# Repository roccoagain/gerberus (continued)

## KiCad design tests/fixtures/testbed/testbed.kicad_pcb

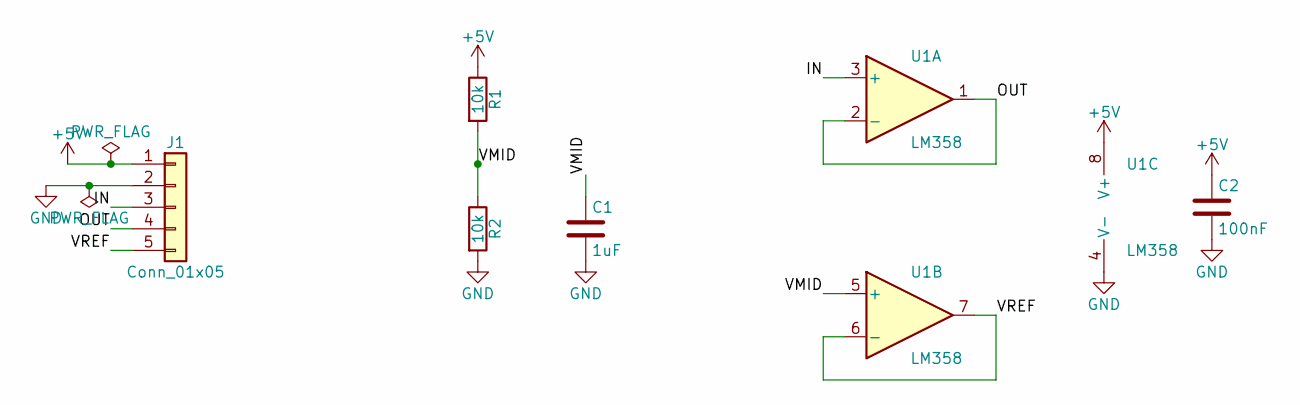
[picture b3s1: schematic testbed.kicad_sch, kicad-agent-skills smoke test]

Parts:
C1: 1uF; C_0603_1608Metric; LCSC C15849
C2: 100nF; C_0603_1608Metric; LCSC C14663
J1: Conn_01x05; PinHeader_1x05_P2.54mm_Vertical; LCSC C2337
R1, R2: 10k; R_0603_1608Metric; LCSC C25804
U1: LM358; SOIC-8_3.9x4.9mm_P1.27mm; MPN LM358DR; LCSC C7950

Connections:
+5V: C2.1, J1.1, R1.1, U1.8 (V+)
/IN: J1.3, U1.3 (+)
/OUT: J1.4, U1.1, U1.2 (-)
/VMID: C1.1, R1.2, R2.1, U1.5 (+)
/VREF: J1.5, U1.6 (-), U1.7
GND: C1.2, C2.2, J1.2, R2.2, U1.4 (V-)

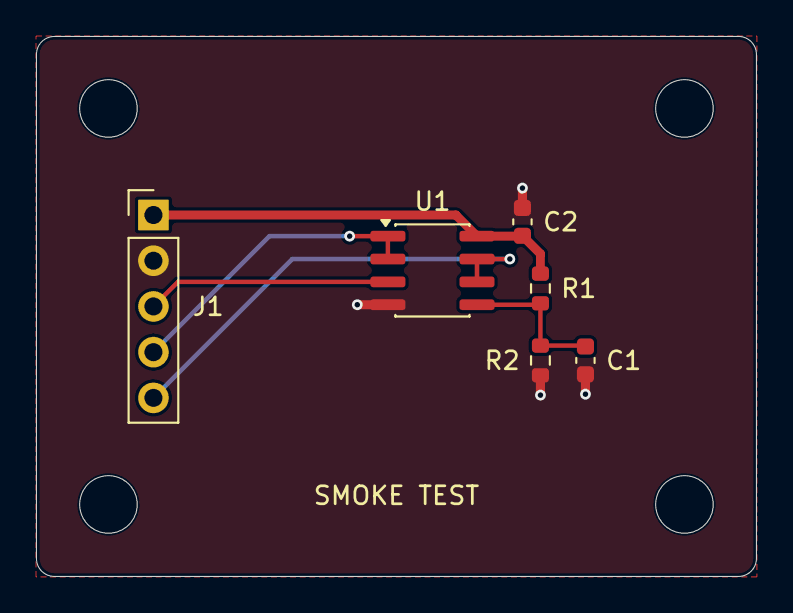
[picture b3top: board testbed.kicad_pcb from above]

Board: 2 copper layers, 40.0 x 30.0 mm, 10 parts (0 on the bottom side), 6 nets.

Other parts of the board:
H1, H2, H3, H4: MountingHole_3.2mm_M3

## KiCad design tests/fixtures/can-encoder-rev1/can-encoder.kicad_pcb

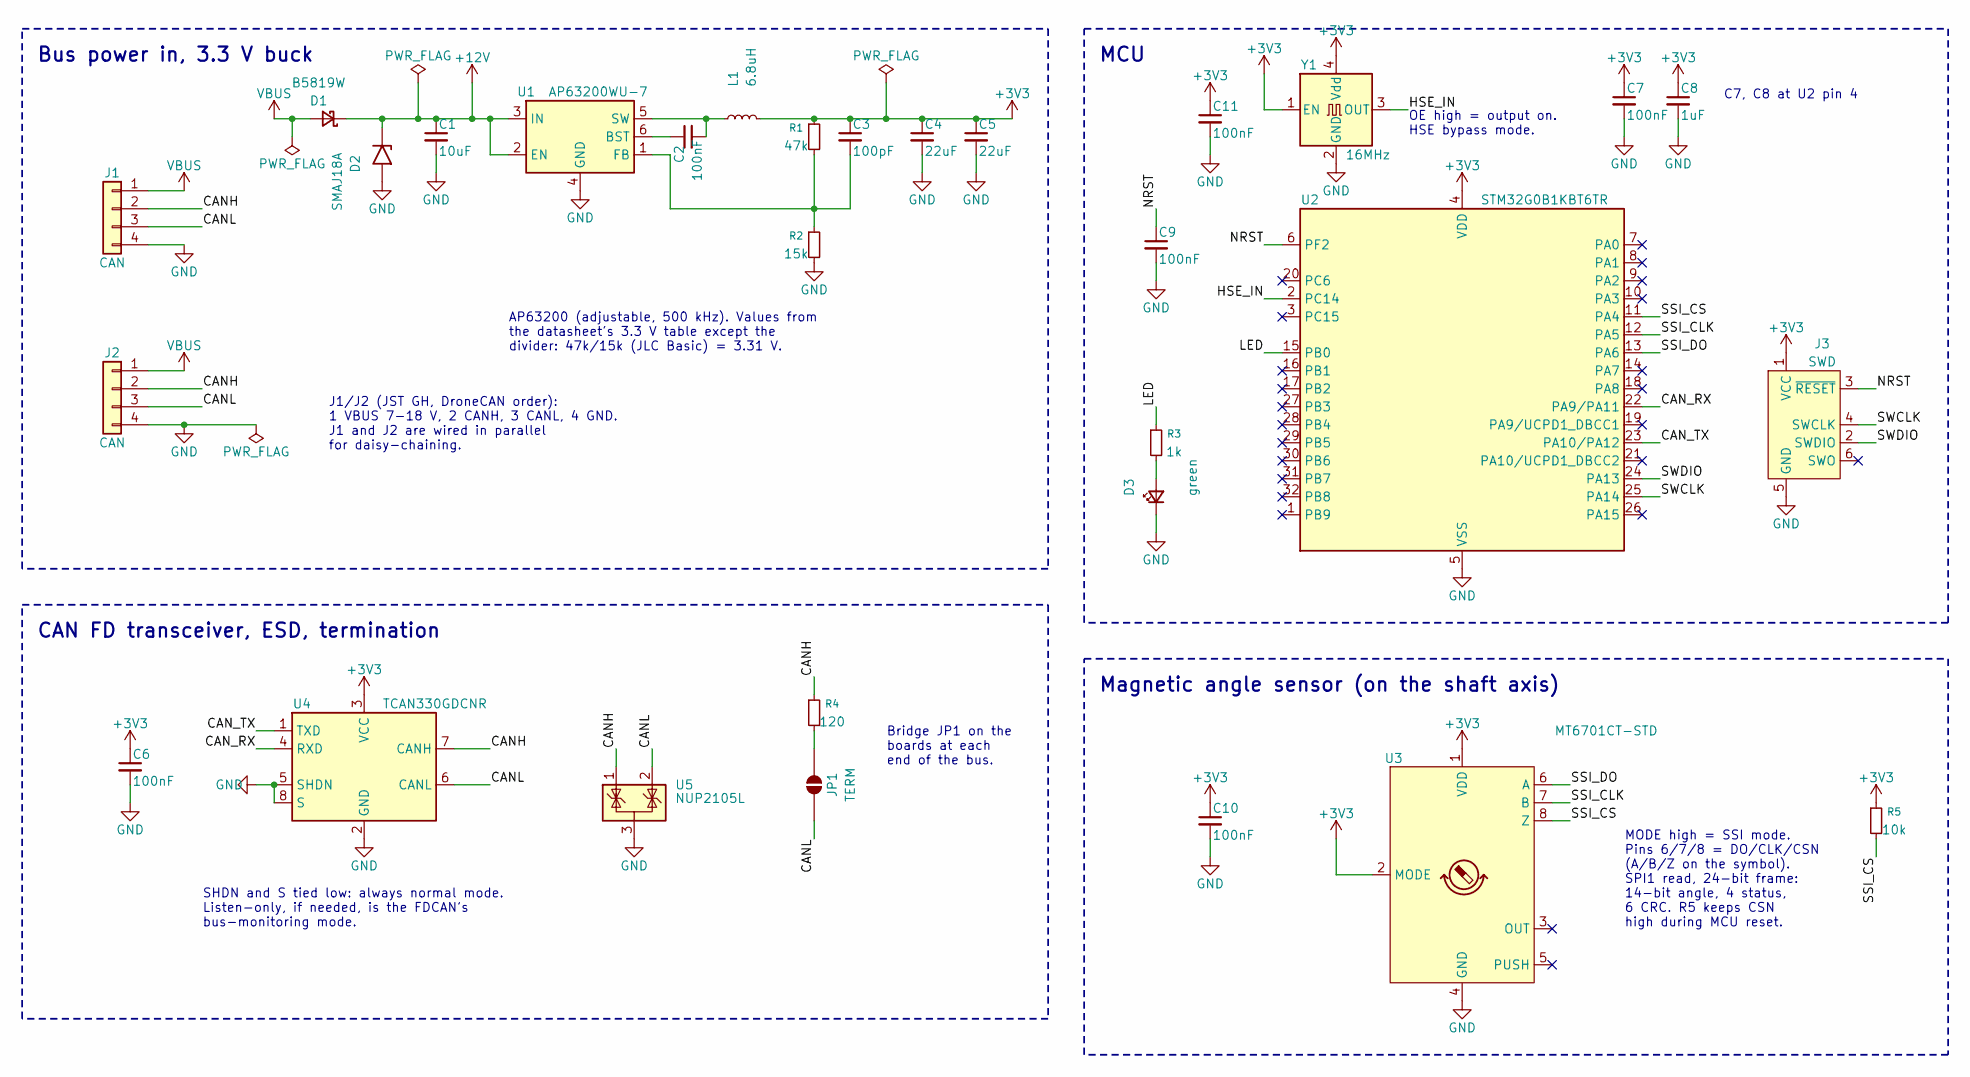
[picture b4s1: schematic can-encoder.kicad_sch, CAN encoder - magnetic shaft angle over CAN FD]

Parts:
C1: 10uF; C_0805_2012Metric; Voltage 50V; MPN GRM21BR61H106KE43L; LCSC C440198
C2, C6, C7, C9, C10, C11: 100nF; C_0402_1005Metric; Voltage 16V; MPN CL05B104KO5NNNC; LCSC C1525
C3: 100pF; C_0402_1005Metric; Voltage 50V; MPN 0402CG101J500NT; LCSC C1546
C4, C5: 22uF; C_0805_2012Metric; Voltage 25V; MPN CL21A226MAQNNNE; LCSC C45783
C8: 1uF; C_0402_1005Metric; Voltage 25V; MPN CL05A105KA5NQNC; LCSC C52923
D1: B5819W; D_SOD-123; MPN B5819W SL; LCSC C8598
D2: SMAJ18A; D_SMA; MPN SMAJ18A; LCSC C173513
D3: green; LED_0805_2012Metric; MPN KT-0805G; LCSC C2297
J1, J2: CAN; JST_GH_SM04B-GHS-TB_1x04-1MP_P1.25mm_Horizontal; MPN SM04B-GHS-TB(LF)(SN); LCSC C189895
J3: SWD; Tag-Connect_TC2030-IDC-NL_2x03_P1.27mm_Vertical
JP1: TERM; SolderJumper-2_P1.3mm_Open_RoundedPad1.0x1.5mm
L1: 6.8uH; L_Changjiang_FNR4030S; MPN FNR4030S6R8MT; LCSC C167876
R1: 47k; R_0402_1005Metric; MPN 0402WGF4702TCE; LCSC C25792
R2: 15k; R_0402_1005Metric; MPN 0402WGF1502TCE; LCSC C25756
R3: 1k; R_0402_1005Metric; MPN 0402WGF1001TCE; LCSC C11702
R4: 120; R_0402_1005Metric; MPN 0402WGF1200TCE; LCSC C25079
R5: 10k; R_0402_1005Metric; MPN 0402WGF1002TCE; LCSC C25744
U1: AP63200WU-7; TSOT-23-6; MPN AP63200WU-7; LCSC C2071868
U2: STM32G0B1KBT6TR; LQFP-32_7x7mm_P0.8mm; MPN STM32G0B1KBT6TR; LCSC C7021416
U3: MT6701CT-STD; SOIC-8_3.9x4.9mm_P1.27mm; MPN MT6701CT-STD-R; LCSC C3003196
U4: TCAN330GDCNR; SOT-23-8; MPN TCAN330GDCNR; LCSC C191006
U5: NUP2105L; SOT-23; MPN NUP2105LT1G; LCSC C14486
Y1: 16MHz; Oscillator_SMD_SiT_PQFN-4Pin_2.0x1.6mm; MPN OT201616MJBA4SL; LCSC C669078

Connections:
+3V3: C3.1, C4.1, C5.1, C6.1, C7.1, C8.1, C10.1, C11.1, J3.1 (VCC), L1.2, R1.1, R5.1, U2.4 (VDD), U3.1 (VDD), U3.2 (MODE), U4.3 (VCC), Y1.1 (EN), Y1.4 (Vdd)
+12V: C1.1, D1.1 (K), D2.1 (A1), U1.2 (EN), U1.3 (IN)
/CANH: J1.2, J2.2, R4.1, U4.7 (CANH), U5.1 (K)
/CANL: J1.3, J2.3, JP1.1 (A), U4.6 (CANL), U5.2 (K)
/CAN_RX: U2.22 (PA9/PA11), U4.4 (RXD)
/CAN_TX: U2.23 (PA10/PA12), U4.1 (TXD)
/HSE_IN: U2.2 (PC14), Y1.3 (OUT)
/LED: R3.1, U2.15 (PB0)
/NRST: C9.1, J3.3 (~RESET), U2.6 (PF2)
/SSI_CLK: U2.12 (PA5), U3.7 (B)
/SSI_CS: R5.2, U2.11 (PA4), U3.8 (Z)
/SSI_DO: U2.13 (PA6), U3.6 (A)
/SWCLK: J3.4 (SWCLK), U2.25 (PA14)
/SWDIO: J3.2 (SWDIO), U2.24 (PA13)
GND: C1.2, C4.2, C5.2, C6.2, C7.2, C8.2, C9.2, C10.2, C11.2, D2.2 (A2), D3.1 (K), J1.4, J2.4, J3.5 (GND), R2.2, U1.4 (GND), U2.5 (VSS), U3.4 (GND), U4.2 (GND), U4.5 (SHDN), U4.8 (S), U5.3 (A), Y1.2 (GND)
unnamed: D3.2 (A), R3.2
unnamed: JP1.2 (B), R4.2
unnamed: C2.1, U1.6 (BST)
unnamed: C3.2, R1.2, R2.1, U1.1 (FB)
unnamed: C2.2, L1.1, U1.5 (SW)
VBUS: D1.2 (A), J1.1, J2.1

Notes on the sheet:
Bus power in, 3.3 V buck
J1/J2 (JST GH, DroneCAN order): 1 VBUS 7-18 V, 2 CANH, 3 CANL, 4 GND. J1 and J2 are wired in parallel for daisy-chaining.
AP63200 (adjustable, 500 kHz). Values from the datasheet's 3.3 V table except the divider: 47k/15k (JLC Basic) = 3.31 V.
CAN FD transceiver, ESD, termination
Bridge JP1 on the boards at each end of the bus.
SHDN and S tied low: always normal mode. Listen-only, if needed, is the FDCAN's bus-monitoring mode.
MCU
C7, C8 at U2 pin 4
OE high = output on. HSE bypass mode.
Magnetic angle sensor (on the shaft axis)
MODE high = SSI mode. Pins 6/7/8 = DO/CLK/CSN (A/B/Z on the symbol). SPI1 read, 24-bit frame: 14-bit angle, 4 status, 6 CRC. R5 keeps CSN high during MCU reset.

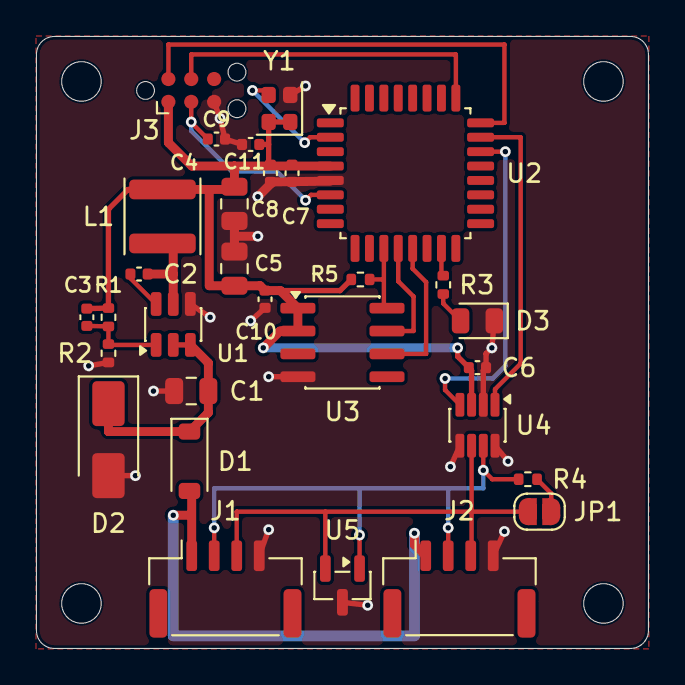
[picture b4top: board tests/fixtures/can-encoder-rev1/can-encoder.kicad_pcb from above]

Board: 2 copper layers, 34.0 x 34.0 mm, 34 parts (0 on the bottom side), 21 nets.

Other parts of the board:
H1, H2, H3, H4: MountingHole_2.2mm_M2

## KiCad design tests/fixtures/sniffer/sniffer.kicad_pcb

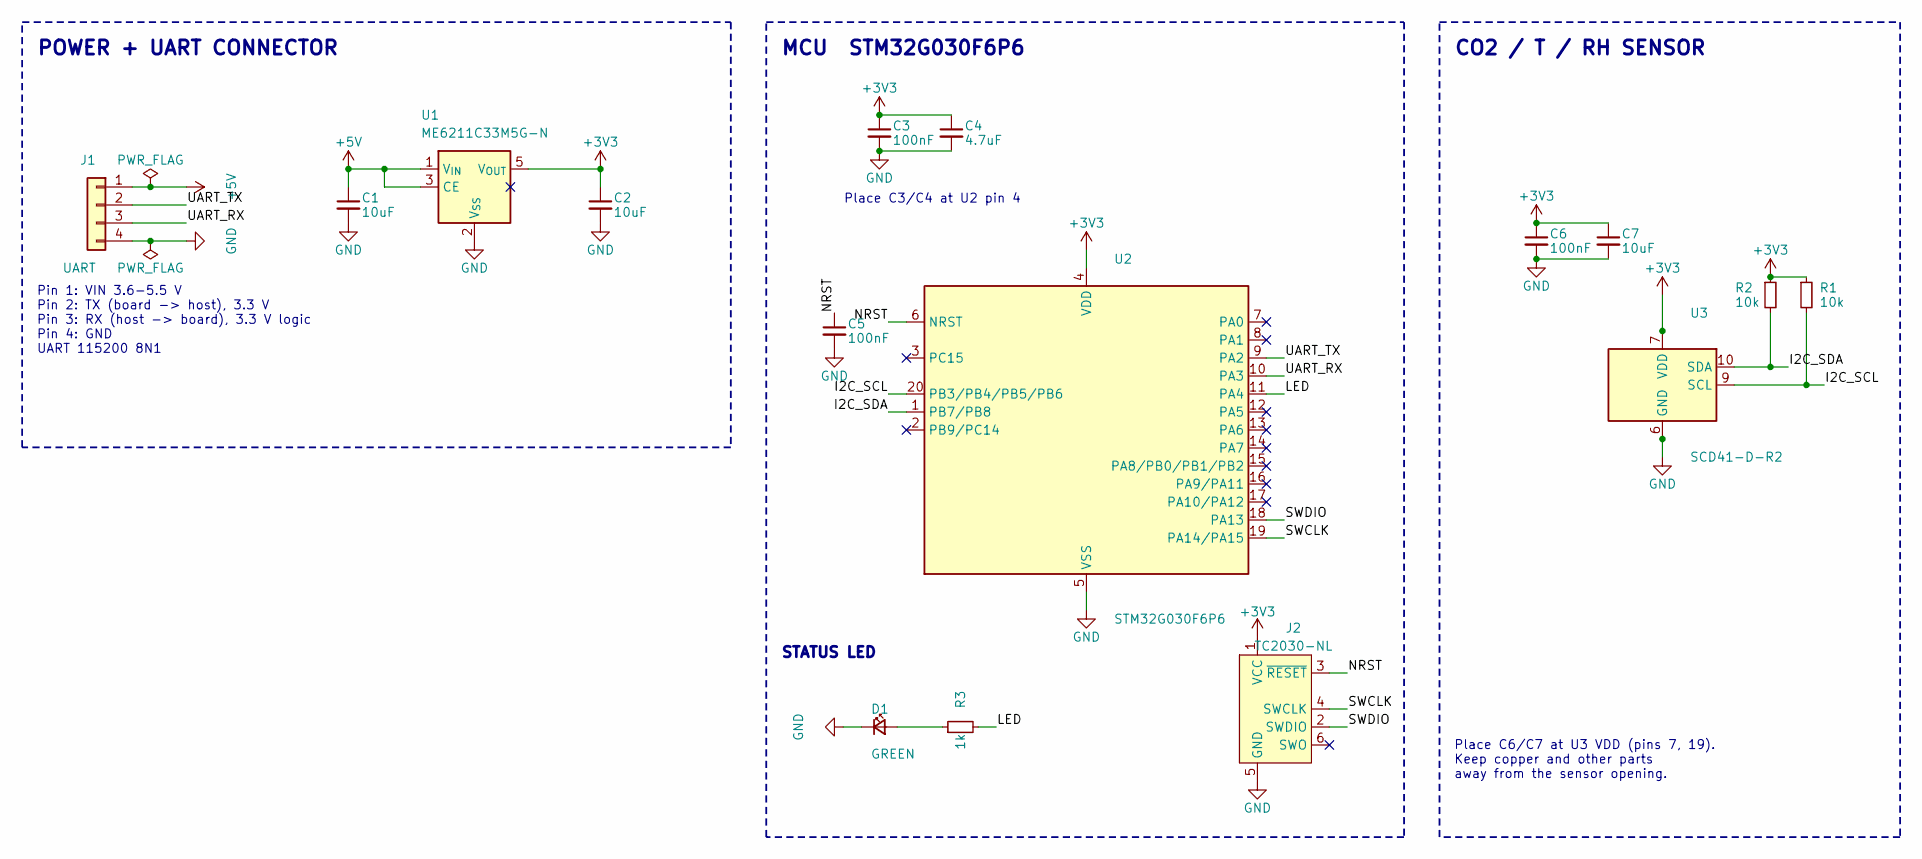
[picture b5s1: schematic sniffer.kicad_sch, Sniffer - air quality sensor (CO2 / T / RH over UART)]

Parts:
C1, C2, C7: 10uF; C_0805_2012Metric; Voltage 25V; MPN CL21A106KAYNNNE; LCSC C15850
C3, C5, C6: 100nF; C_0603_1608Metric; Voltage 50V; MPN CC0603KRX7R9BB104; LCSC C14663
C4: 4.7uF; C_0603_1608Metric; Voltage 16V; MPN CL10A475KO8NNNC; LCSC C19666
D1: GREEN; LED_0805_2012Metric; MPN KT-0805G; LCSC C2297
J1: UART; JST_SH_SM04B-SRSS-TB_1x04-1MP_P1.00mm_Horizontal; MPN SM04B-SRSS-TB(LF)(SN); LCSC C160404
J2: TC2030-NL; Tag-Connect_TC2030-IDC-NL_2x03_P1.27mm_Vertical
R1, R2: 10k; R_0603_1608Metric; MPN 0603WAF1002T5E; LCSC C25804
R3: 1k; R_0603_1608Metric; MPN 0603WAF1001T5E; LCSC C21190
U1: ME6211C33M5G-N; SOT-23-5; MPN ME6211C33M5G-N; LCSC C82942
U2: STM32G030F6P6; TSSOP-20_4.4x6.5mm_P0.65mm; MPN STM32G030F6P6TR; LCSC C529330
U3: SCD41-D-R2; Sensirion_SCD4x-1EP_10.1x10.1mm_P1.25mm_EP4.8x4.8mm; MPN SCD41-D-R2; LCSC C3659294

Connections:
+3V3: C2.1, C3.1, C4.1, C6.1, C7.1, J2.1 (VCC), R1.1, R2.1, U1.5 (V_{OUT}), U2.4 (VDD), U3.7 (VDD), U3.19 (VDD)
+5V: C1.1, J1.1, U1.1 (V_{IN}), U1.3 (CE)
/I2C_SCL: R1.2, U2.20 (PB3/PB4/PB5/PB6), U3.9 (SCL)
/I2C_SDA: R2.2, U2.1 (PB7/PB8), U3.10 (SDA)
/LED: R3.2, U2.11 (PA4)
/NRST: C5.1, J2.3 (~RESET), U2.6 (NRST)
/SWCLK: J2.4 (SWCLK), U2.19 (PA14/PA15)
/SWDIO: J2.2 (SWDIO), U2.18 (PA13)
/UART_RX: J1.3, U2.10 (PA3)
/UART_TX: J1.2, U2.9 (PA2)
GND: C1.2, C2.2, C3.2, C4.2, C5.2, C6.2, C7.2, D1.1 (K), J1.4, J2.5 (GND), U1.2 (V_{SS}), U2.5 (VSS), U3.6 (GND), U3.20 (GND), U3.21 (GND)
unnamed: D1.2 (A), R3.1

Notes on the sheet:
POWER + UART CONNECTOR
Pin 1: VIN 3.6-5.5 V Pin 2: TX (board -> host), 3.3 V Pin 3: RX (host -> board), 3.3 V logic Pin 4: GND UART 115200 8N1
MCU STM32G030F6P6
Place C3/C4 at U2 pin 4
STATUS LED
CO2 / T / RH SENSOR
Place C6/C7 at U3 VDD (pins 7, 19). Keep copper and other parts away from the sensor opening.

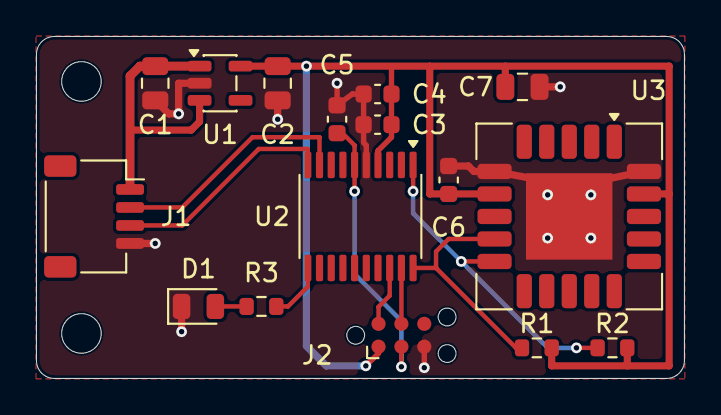
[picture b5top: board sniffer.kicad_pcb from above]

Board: 2 copper layers, 36.0 x 19.0 mm, 18 parts (0 on the bottom side), 12 nets.

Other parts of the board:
H1, H2: MountingHole_2.2mm_M2

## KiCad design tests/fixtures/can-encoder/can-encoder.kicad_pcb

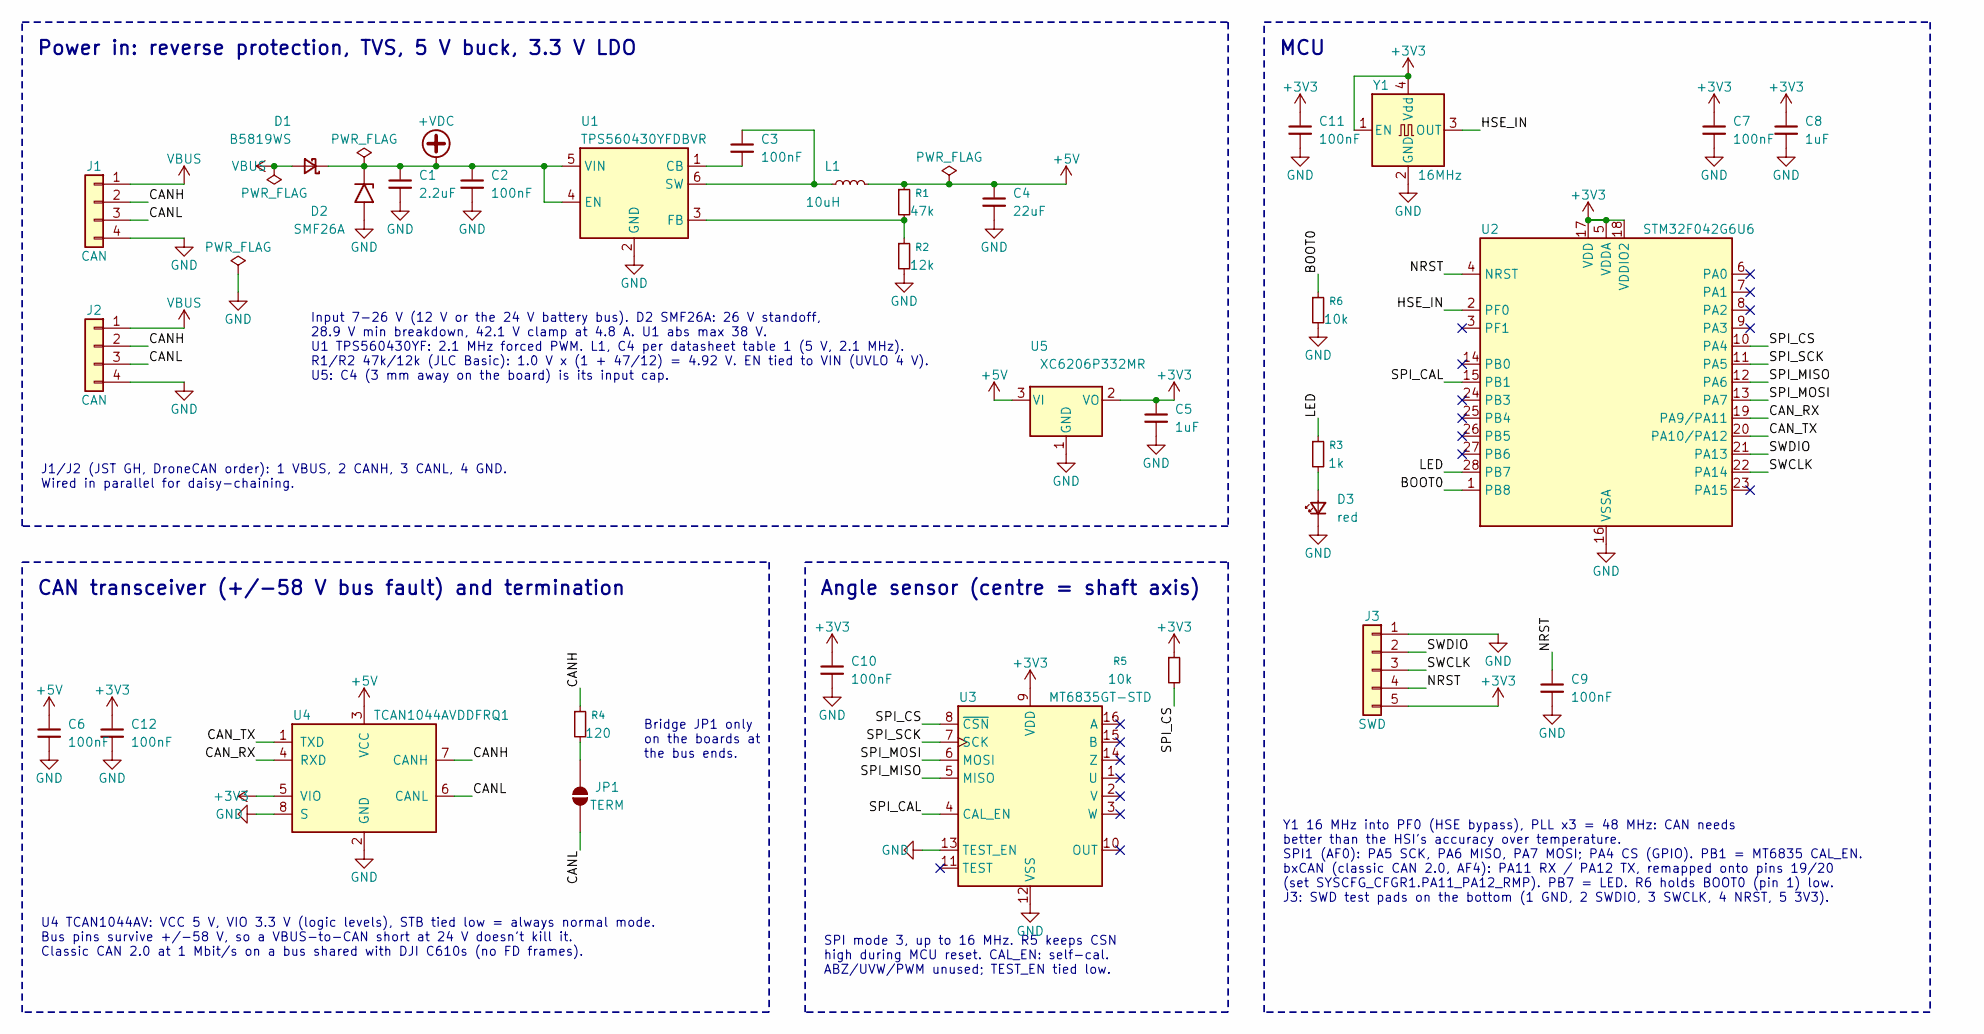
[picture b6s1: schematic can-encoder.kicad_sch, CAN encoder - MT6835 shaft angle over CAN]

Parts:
C1: 2.2uF; C_0805_2012Metric; Voltage 50V; MPN CC0805KKX7R9BB225; LCSC C125847
C2: 100nF; C_0402_1005Metric; Voltage 50V; MPN CL05B104KB54PNC; LCSC C307331
C3, C6, C7, C9, C10, C11, C12: 100nF; C_0402_1005Metric; Voltage 16V; MPN CL05B104KO5NNNC; LCSC C1525
C4: 22uF; C_0805_2012Metric; Voltage 25V; MPN CL21A226MAQNNNE; LCSC C45783
C5, C8: 1uF; C_0402_1005Metric; Voltage 25V; MPN CL05A105KA5NQNC; LCSC C52923
D1: B5819WS; D_SOD-323; MPN B5819WS; LCSC C22624
D2: SMF26A; D_SOD-123F; MPN SMF26A; LCSC C123789
D3: red; LED_0603_1608Metric; MPN KT-0603R; LCSC C2286
J1, J2: CAN; JST_GH_SM04B-GHS-TB_1x04-1MP_P1.25mm_Horizontal; MPN SM04B-GHS-TB(LF)(SN); LCSC C189895
J3: SWD; SWD_Pads_1x05_P1.27mm
JP1: TERM; SolderJumper-2_P1.3mm_Open_RoundedPad1.0x1.5mm
L1: 10uH; L_Sunlord_SWPA252012S; MPN SWPA252012S100MT; LCSC C37428
R1: 47k; R_0402_1005Metric; MPN 0402WGF4702TCE; LCSC C25792
R2: 12k; R_0402_1005Metric; MPN 0402WGF1202TCE; LCSC C25752
R3: 1k; R_0402_1005Metric; MPN 0402WGF1001TCE; LCSC C11702
R4: 120; R_0402_1005Metric; MPN 0402WGF1200TCE; LCSC C25079
R5, R6: 10k; R_0402_1005Metric; MPN 0402WGF1002TCE; LCSC C25744
U1: TPS560430YFDBVR; SOT-23-6; MPN TPS560430YFDBVR; LCSC C962155
U2: STM32F042G6U6; QFN-28_4x4mm_P0.5mm; MPN STM32F042G6U6TR; LCSC C2971720
U3: MT6835GT-STD; TSSOP-16_4.4x5mm_P0.65mm; MPN MT6835GT-STD-R; LCSC C2932578
U4: TCAN1044AVDDFRQ1; SOT-23-8; MPN TCAN1044AVDDFRQ1; LCSC C3236207
U5: XC6206P332MR; SOT-23-3; MPN XC6206P332MR-G; LCSC C5446
Y1: 16MHz; Oscillator_SMD_SiT_PQFN-4Pin_2.0x1.6mm; MPN OT201616MJBA4SL; LCSC C669078

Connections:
+3V3: C5.1, C7.1, C8.1, C10.1, C11.1, C12.1, J3.5, R5.1, U2.5 (VDDA), U2.17 (VDD), U2.18 (VDDIO2), U3.9 (VDD), U4.5 (VIO), U5.2 (VO), Y1.1 (EN), Y1.4 (Vdd)
+5V: C4.1, C6.1, L1.2, R1.1, U4.3 (VCC), U5.3 (VI)
+VDC: C1.1, C2.1, D1.1 (K), D2.1 (A1), U1.4 (EN), U1.5 (VIN)
/BOOT0: R6.1, U2.1 (PB8)
/CANH: J1.2, J2.2, R4.1, U4.7 (CANH)
/CANL: J1.3, J2.3, JP1.1 (A), U4.6 (CANL)
/CAN_RX: U2.19 (PA9/PA11), U4.4 (RXD)
/CAN_TX: U2.20 (PA10/PA12), U4.1 (TXD)
/HSE_IN: U2.2 (PF0), Y1.3 (OUT)
/LED: R3.1, U2.28 (PB7)
/NRST: C9.1, J3.4, U2.4 (NRST)
/SPI_CAL: U2.15 (PB1), U3.4 (CAL_EN)
/SPI_CS: R5.2, U2.10 (PA4), U3.8 (~CSN)
/SPI_MISO: U2.12 (PA6), U3.5 (MISO)
/SPI_MOSI: U2.13 (PA7), U3.6 (MOSI)
/SPI_SCK: U2.11 (PA5), U3.7 (SCK)
/SWCLK: J3.3, U2.22 (PA14)
/SWDIO: J3.2, U2.21 (PA13)
GND: C1.2, C2.2, C4.2, C5.2, C6.2, C7.2, C8.2, C9.2, C10.2, C11.2, C12.2, D2.2 (A2), D3.1 (K), J1.4, J2.4, J3.1, R2.2, R6.2, U1.2 (GND), U2.16 (VSSA), U3.12 (VSS), U3.13 (TEST_EN), U4.2 (GND), U4.8 (S), U5.1 (GND), Y1.2 (GND)
unnamed: D3.2 (A), R3.2
unnamed: JP1.2 (B), R4.2
unnamed: C3.2, U1.1 (CB)
unnamed: R1.2, R2.1, U1.3 (FB)
unnamed: C3.1, L1.1, U1.6 (SW)
VBUS: D1.2 (A), J1.1, J2.1

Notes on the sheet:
Power in: reverse protection, TVS, 5 V buck, 3.3 V LDO
Input 7-26 V (12 V or the 24 V battery bus). D2 SMF26A: 26 V standoff, 28.9 V min breakdown, 42.1 V clamp at 4.8 A. U1 abs max 38 V. U1 TPS560430YF: 2.1 MHz forced PWM. L1, C4 per datasheet table 1 (5 V, 2.1 MHz). R1/R2 47k/12k (JLC Basic): 1.0 V x (1 + 47/12) = 4.92 V. EN tied to VIN (UVLO 4 V). U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
J1/J2 (JST GH, DroneCAN order): 1 VBUS, 2 CANH, 3 CANL, 4 GND. Wired in parallel for daisy-chaining.
CAN transceiver (+/-58 V bus fault) and termination
U4 TCAN1044AV: VCC 5 V, VIO 3.3 V (logic levels), STB tied low = always normal mode. Bus pins survive +/-58 V, so a VBUS-to-CAN short at 24 V doesn't kill it. Classic CAN 2.0 at 1 Mbit/s on a bus shared with DJI C610s (no FD frames).
Bridge JP1 only on the boards at the bus ends.
MCU
Y1 16 MHz into PF0 (HSE bypass), PLL x3 = 48 MHz: CAN needs better than the HSI's accuracy over temperature. SPI1 (AF0): PA5 SCK, PA6 MISO, PA7 MOSI; PA4 CS (GPIO). PB1 = MT6835 CAL_EN. bxCAN (classic CAN 2.0, AF4): PA11 RX / PA12 TX, remapped onto pins 19/20 (set SYSCFG_CFGR1.PA11_PA12_RMP). PB7 =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
Angle sensor (centre = shaft axis)
SPI mode 3, up to 16 MHz. R5 keeps CSN high during MCU reset. CAL_EN: self-cal. ABZ/UVW/PWM unused; TEST_EN tied low.

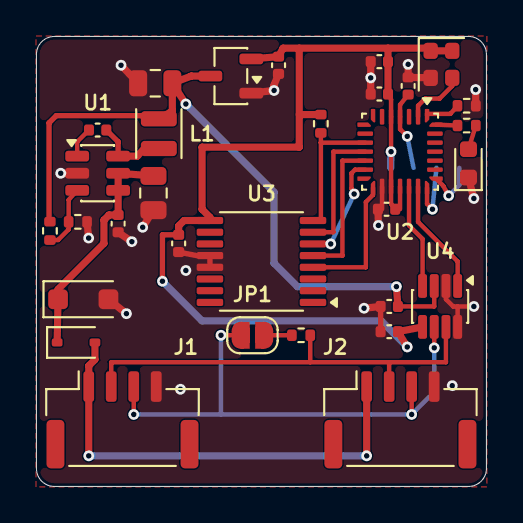
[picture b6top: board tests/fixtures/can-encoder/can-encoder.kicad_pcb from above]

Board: 2 copper layers, 25.0 x 25.0 mm, 32 parts (1 on the bottom side), 25 nets.

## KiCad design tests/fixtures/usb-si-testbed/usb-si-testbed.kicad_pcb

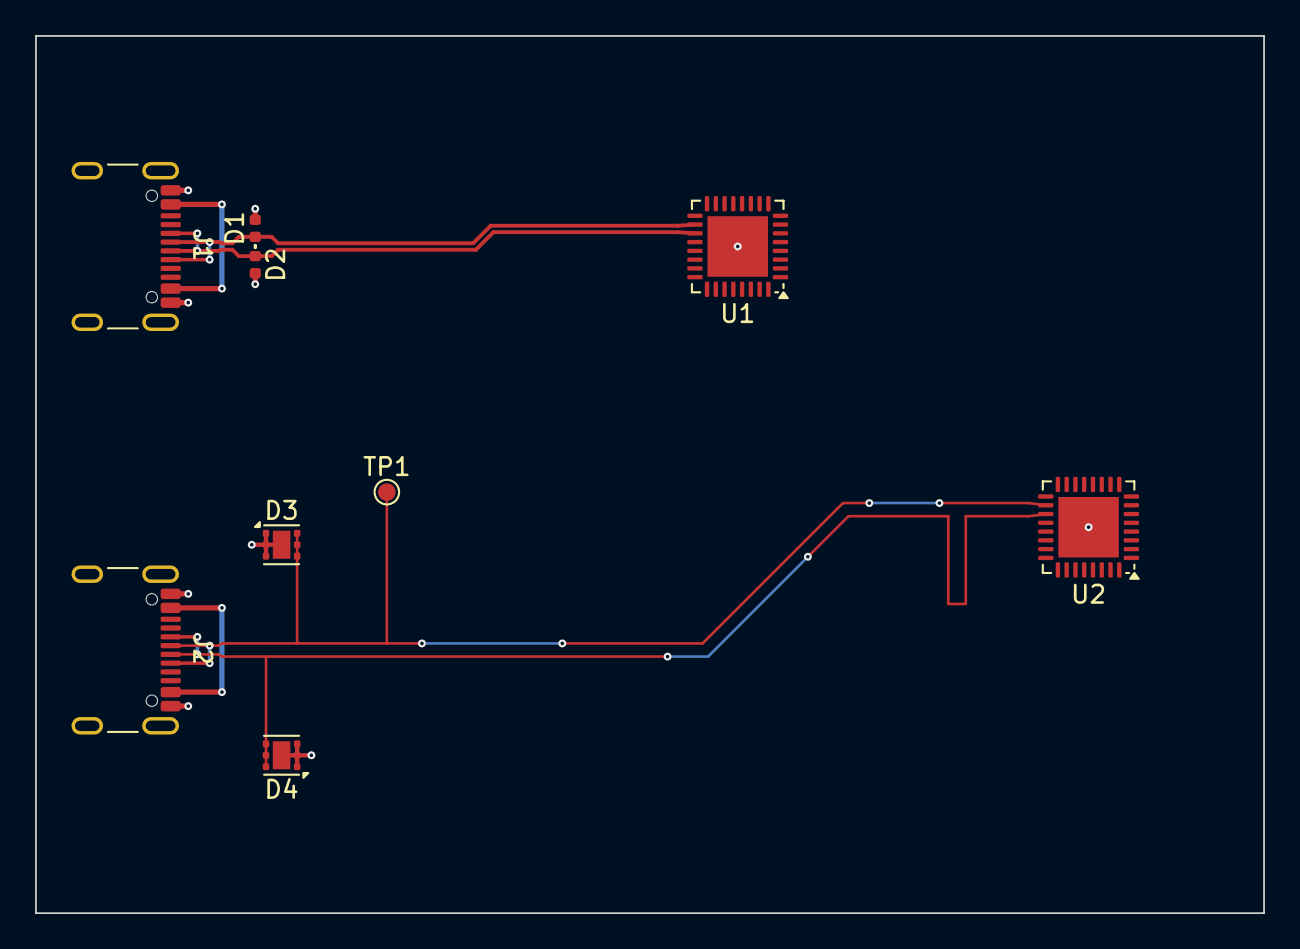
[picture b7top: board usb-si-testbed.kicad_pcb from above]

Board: 4 copper layers, 70.0 x 50.0 mm, 9 parts (0 on the bottom side), 7 nets.

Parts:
D1, D2: TPD1E05U06DPYR; D_0402_1005Metric
D3, D4: TVS0500DRVR; WSON-6-1EP_2x2mm_P0.65mm_EP1x1.6mm
J1, J2: USB4105-GF-A; USB_C_Receptacle_GCT_USB4105-xx-A_16P_TopMnt_Horizontal
TP1: TP; TestPoint_Pad_D1.0mm
U1, U2: TUSB1210BRHBR; Texas_RHB0032E_VQFN-32-1EP_5x5mm_P0.5mm_EP3.45x3.45mm

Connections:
GND: D1.2, D2.2, D3.1, D3.2, D3.3, D3.7, D4.1, D4.2, D4.3, D4.7, J1.A1, J1.A12, J1.B1, J1.B12, J1.S1, J2.A1, J2.A12, J2.B1, J2.B12, J2.S1, U1.33, U2.33
USB1_D+: D1.1, J1.A6, J1.B6, U1.18
USB1_D-: D2.1, J1.A7, J1.B7, U1.19
USB2_D+: D3.4, D3.5, D3.6, J2.A6, J2.B6, TP1.1, U2.18
USB2_D-: D4.4, D4.5, D4.6, J2.A7, J2.B7, U2.19
VBUS1: J1.A4, J1.A9, J1.B4, J1.B9
VBUS2: J2.A4, J2.A9, J2.B4, J2.B9

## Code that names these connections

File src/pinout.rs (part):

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//!
//! Numbers must line up: a symbol pin with no pad never reaches copper, and a datasheet pin with no symbol pin
//! is left floating on the board. Names are compared loosely (case, KiCad markup, alternate functions written
//! as `PA9/PA11`, and a few common synonyms such as `GND`/`VSS`), because symbols rarely copy the datasheet
//! letter for letter. A name that matches a *different* datasheet pin is reported as a swap, which is an
//! error. Any other name difference is a warning for a person to look at, never a pass or a fail by guesswork.
use std::collections::{BTreeMap, BTreeSet};
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        .collect()
}

/// The words in a name: `PA9/PA11`, `PA11 [PA9]` and `PB8-BOOT0` each name two signals. A trailing `-` or
/// `+` (`V-`, `IN+`) stays part of the word. `Pin_3` is `3`.
fn tokens(name: &str) -> BTreeSet<String> {
    let shown = shown_name(name).unwrap_or_default().to_ascii_uppercase();
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        if word.is_empty() {
            continue;
        }
        // `PB8-BOOT0` and `PF0-OSC_IN` are a port pin and its alternate function. Other hyphenated names
        // (`LED-A`, `VDD-IO`) are one name, so they are split only after a port pin.
        let pieces: Vec<&str> = match word.split_once('-') {
            Some((port, rest)) if is_port_pin(port) && !rest.is_empty() => std::iter::once(port)
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    !word.starts_with('-') && !word.ends_with('-') && !word.contains('+')
}

/// A microcontroller port pin such as `PA9` or `PB12`.
fn is_port_pin(word: &str) -> bool {
    let mut c = word.chars();
    c.next() == Some('P') && c.next().is_some_and(|ch| ch.is_ascii_uppercase()) && {
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        assert!(names_match("~{CSN}", "CSN"));
        assert!(names_match("V_{IN}", "VIN"));
        assert!(names_match("Vdd", "VDD"));
        assert!(names_match("PA9/PA11", "PA11 [PA9]"));
        assert!(names_match("PB8", "PB8-BOOT0"));
        assert!(names_match("VDD", "VDD/VDDA"));
        assert!(names_match("Pin_3", "3"));
        assert!(names_match("VSSA", "VSS"));
        assert!(names_match("EN", "TRI-STATE"));
        assert!(names_match("OUT", "OUTPUT"));
        assert!(names_match("V-", "V-"));
        assert!(names_match("PF0", "PF0-OSC_IN"));
        assert!(names_match("PA14/PA15", "PA14-BOOT0/PA15"));
        assert!(names_match("IN+", "IN+"));
        assert!(names_match("V-", "V–"));
        assert!(names_match("-", "–IN"));
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        assert!(!names_match("A1", "K"));
        assert!(!names_match("VDD", "VDDH"));
        assert!(!names_match("S", "STB"));
        assert!(!names_match("PA9", "PA10"));
        assert!(!names_match("TXD", "RXD"));
        assert!(!names_match("IN+", "IN-"));
        assert!(!names_match("+IN", "-IN"));
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
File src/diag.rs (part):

//! Terminal output in the style of rustc's diagnostics:
//!
//! ```text
//! error[abs-max]: U6.PA4 reaches 26 V, past the maximum of 4 V
//!   --> U6.PA4 (/mcu/VSENSE)
//!    = help: add a divider, clamp or series resistor, or choose a part rated higher
//! ```
//!
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
    /// Splits a checker's message into headline, location and notes. `subjects` are what the finding is about: a
    /// reference designator, or a pair's nets. A message that opens with one and a colon, like
    /// `U6.PA4 (/mcu/VSENSE): ...`, gives its location from that opening.
    pub fn from_message(level: Level, rule: &str, subjects: &[&str], message: &str) -> Diagnostic {
        let mut segs = split_top(message, ": ");
        let mut location = None;
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    None
}

/// Verbs a claim can open with, so the headline reads `U6.PA4 reaches 26 V` rather than `U6.PA4: reaches 26 V`.
const VERBS: [&str; 18] = [
    "is",
    "are",
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    "needs",
];

/// Whether an opening like `U6.PA4 (/mcu/VSENSE)` or `R15.1 (/LED0) from R15.2 (/LED0_A)` only says where.
fn is_locator(seg: &str, subjects: &[&str]) -> bool {
    let bare = without_parens(seg);
    let words: Vec<&str> = bare.split_whitespace().collect();
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        && (words.len() == 1 || ["from", "to", "between"].contains(&words[1]))
}

/// Whether `word` is one of `subjects`, or a pin of one: `U6` or `U6.PA4` for `U6`.
fn names(word: &str, subjects: &[&str]) -> bool {
    subjects
        .iter()
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        let g = d(
            "abs-max",
            "U6",
            "U6.PA4 (/mcu/VSENSE): 0 to 26 V: reaches 26 V, past the maximum of 4 V (STM32G0B1KBT6TR DS13560 Rev 3 \
             p66, any pin other than FT_xx)",
        );
        assert_eq!(g.headline, "U6.PA4 reaches 26 V, past the maximum of 4 V");
        assert_eq!(g.location.as_deref(), Some("U6.PA4 (/mcu/VSENSE)"));
        assert_eq!(
            g.notes,
            [
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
